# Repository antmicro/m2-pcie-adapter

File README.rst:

===========================
M.2 to PCIe x4 adapter card
===========================

Copyright (c) 2020-2021 Antmicro <`www.antmicro.com <https://www.antmicro.com>`_>

.. image:: img/pcie-adapter.jpg
   :scale: 40%

Overview
========

This repository contains open hardware design files for an adapter card created to expose the Peripheral Component Interconnect Express (PCIe) signals available on the M.2 (key M) connector in a regular PCIe x4 edge card socket.
This board has been designed as an extension of the Antmicro's `Jetson Nano Baseboard <https://github.com/antmicro/jetson-nano-baseboard>`_.
It allows the use of regular PCIe expansion cards and accessories with the NVIDIA `Jetson Nano <https://www.nvidia.com/en-us/autonomous-machines/embedded-systems/jetson-nano/>`_ and NVIDIA `Jetson Xavier NX <https://www.nvidia.com/en-us/autonomous-machines/embedded-systems/jetson-xavier-nx/>`_ system on modules.

Key features
============

* M.2 (key-M) edge connector
* PCIe x4 EdgeMount connector (Samtec PCIE-064-02-F-D-EMS2)
* external power supply connector (Molex 22053041)
* Nano Baseboard power supply pogo pins (Harwin P70-1000045R)

The PCB project files were prepared in KiCAD.

Board layout & dimensions
=========================

The picture below presents the general layout and dimensions of the PCB.

.. figure:: img/pcie-adapter-layout.png

Getting started
===============

The PCB design does not include any active components.
It simply passes the signals from the M.2 connector to the PCIe card edge socket.
The final thickness of the PCB should be 0.8mm to make it fit in the M.2 slots.
Since most PCIe card edge connectors are adjusted for 1.55mm, some mechanical tooling is required to assemble the PCIe socket on the PCB.

License
=======

`Apache-2.0 <LICENSE>`_

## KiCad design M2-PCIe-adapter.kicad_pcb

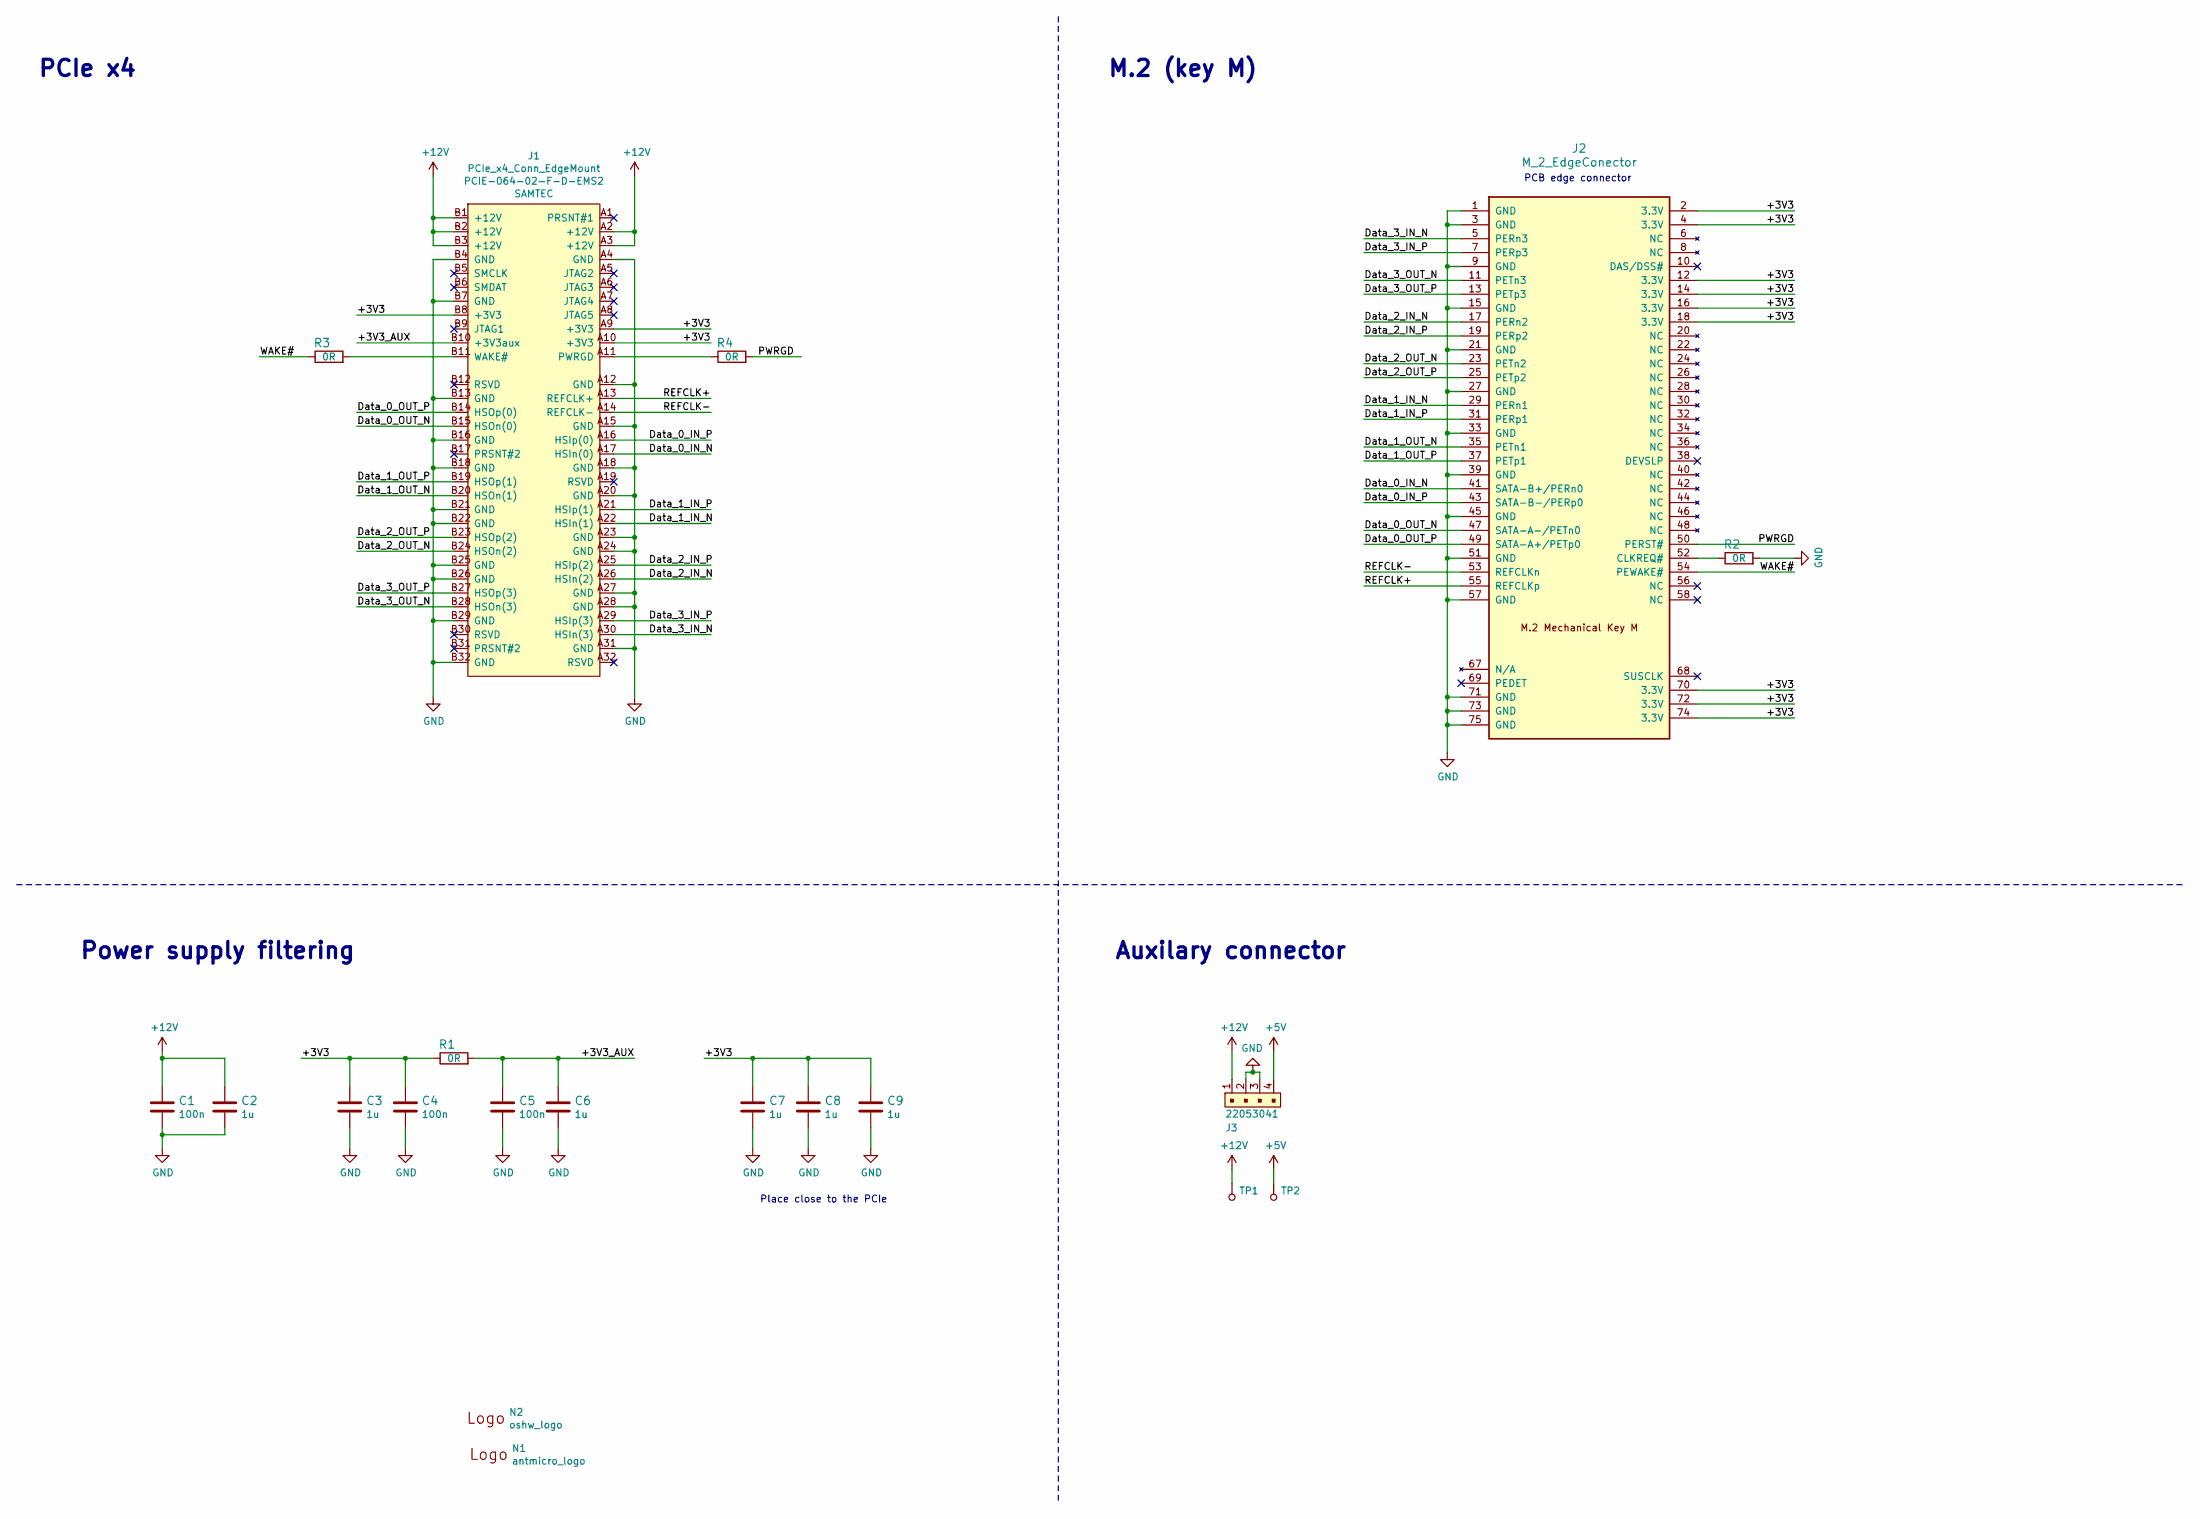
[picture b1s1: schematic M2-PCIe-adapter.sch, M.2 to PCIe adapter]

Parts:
C1, C4, C5: C_100n_0402_16V; 0402-cap; MPN MC0402B104K160CT
C2, C3, C6, C7, C8, C9: C_1u_0603; 0603-cap; MPN 0603X105K160CT
J1: PCIe_x4_Conn_EdgeMount; PCIE-064-02-X-D-EMSX; MPN PCIE-064-02-F-D-EMS2
J2: M_2_EdgeConector; M_2_EdgeConnector
J3: 22053041; MPN 22053041
N1: antmicro_logo; antmicro-logo_scaled_20mm
N2: oshw_logo; oshw-logo
R1, R2, R3, R4: R_0R_0402; 0402-res; MPN ERJ2GE0R00X
TP1, TP2: P70-1000045R; MPN P70-1000045R

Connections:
+5V: J3.4, TP2.1
+12V: C1.1, C2.1, J1.A2 (+12V), J1.A3 (+12V), J1.B1 (+12V), J1.B2 (+12V), J1.B3 (+12V), J3.1, TP1.1
/+3V3: C3.1, C4.1, C7.1, C8.1, C9.1, J1.A9 (+3V3), J1.A10 (+3V3), J1.B8 (+3V3), J2.2 (3.3V), J2.4 (3.3V), J2.12 (3.3V), J2.14 (3.3V), J2.16 (3.3V), J2.18 (3.3V), J2.70 (3.3V), J2.72 (3.3V), J2.74 (3.3V), R1.1
/+3V3_AUX: C5.1, C6.1, J1.B10 (+3V3aux), R1.2
/Data_0_IN_N: J1.A17 (HSIn(0)), J2.41 (SATA-B+/PERn0)
/Data_0_IN_P: J1.A16 (HSIp(0)), J2.43 (SATA-B-/PERp0)
/Data_0_OUT_N: J1.B15 (HSOn(0)), J2.47 (SATA-A-/PETn0)
/Data_0_OUT_P: J1.B14 (HSOp(0)), J2.49 (SATA-A+/PETp0)
/Data_1_IN_N: J1.A22 (HSIn(1)), J2.29 (PERn1)
/Data_1_IN_P: J1.A21 (HSIp(1)), J2.31 (PERp1)
/Data_1_OUT_N: J1.B20 (HSOn(1)), J2.35 (PETn1)
/Data_1_OUT_P: J1.B19 (HSOp(1)), J2.37 (PETp1)
/Data_2_IN_N: J1.A26 (HSIn(2)), J2.17 (PERn2)
/Data_2_IN_P: J1.A25 (HSIp(2)), J2.19 (PERp2)
/Data_2_OUT_N: J1.B24 (HSOn(2)), J2.23 (PETn2)
/Data_2_OUT_P: J1.B23 (HSOp(2)), J2.25 (PETp2)
/Data_3_IN_N: J1.A30 (HSIn(3)), J2.5 (PERn3)
/Data_3_IN_P: J1.A29 (HSIp(3)), J2.7 (PERp3)
/Data_3_OUT_N: J1.B28 (HSOn(3)), J2.11 (PETn3)
/Data_3_OUT_P: J1.B27 (HSOp(3)), J2.13 (PETp3)
/PWRGD: J2.50 (PERST#), R4.2
/REFCLK+: J1.A13 (REFCLK+), J2.55 (REFCLKp)
/REFCLK-: J1.A14 (REFCLK-), J2.53 (REFCLKn)
/WAKE#: J2.54 (PEWAKE#), R3.1
GND: C1.2, C2.2, C3.2, C4.2, C5.2, C6.2, C7.2, C8.2, C9.2, J1.A4 (GND), J1.A12 (GND), J1.A15 (GND), J1.A18 (GND), J1.A20 (GND), J1.A23 (GND), J1.A24 (GND), J1.A27 (GND), J1.A28 (GND), J1.A31 (GND), J1.B4 (GND), J1.B7 (GND), J1.B13 (GND), J1.B16 (GND), J1.B18 (GND), J1.B21 (GND), J1.B22 (GND), J1.B25 (GND), J1.B26 (GND), J1.B29 (GND), J1.B32 (GND), J2.1 (GND), J2.3 (GND), J2.9 (GND), J2.15 (GND), J2.21 (GND), J2.27 (GND), J2.33 (GND), J2.39 (GND), J2.45 (GND), J2.51 (GND), J2.57 (GND), J2.71 (GND), J2.73 (GND), J2.75 (GND), J3.2, J3.3, R2.2
unnamed: J1.A11 (PWRGD), R4.1
unnamed: J1.B11 (WAKE#), R3.2
unnamed: J2.52 (CLKREQ#), R2.1

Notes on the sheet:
Power supply filtering
Place close to the PCIe
PCIe x4
M.2 (key M)
PCB edge connector
Auxilary connector

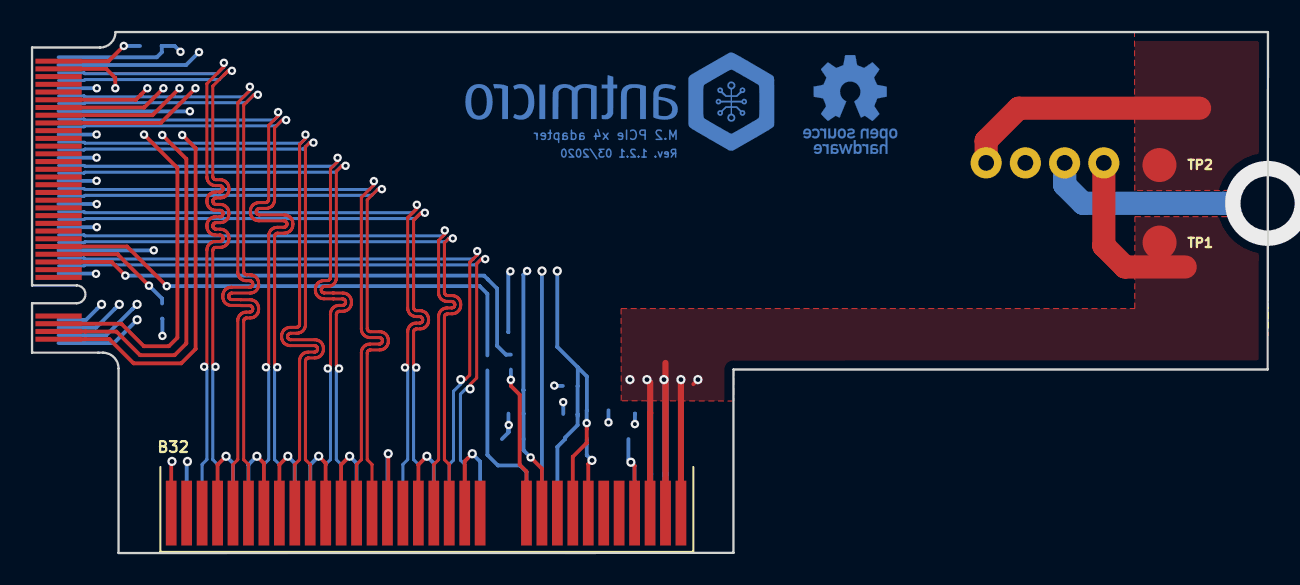
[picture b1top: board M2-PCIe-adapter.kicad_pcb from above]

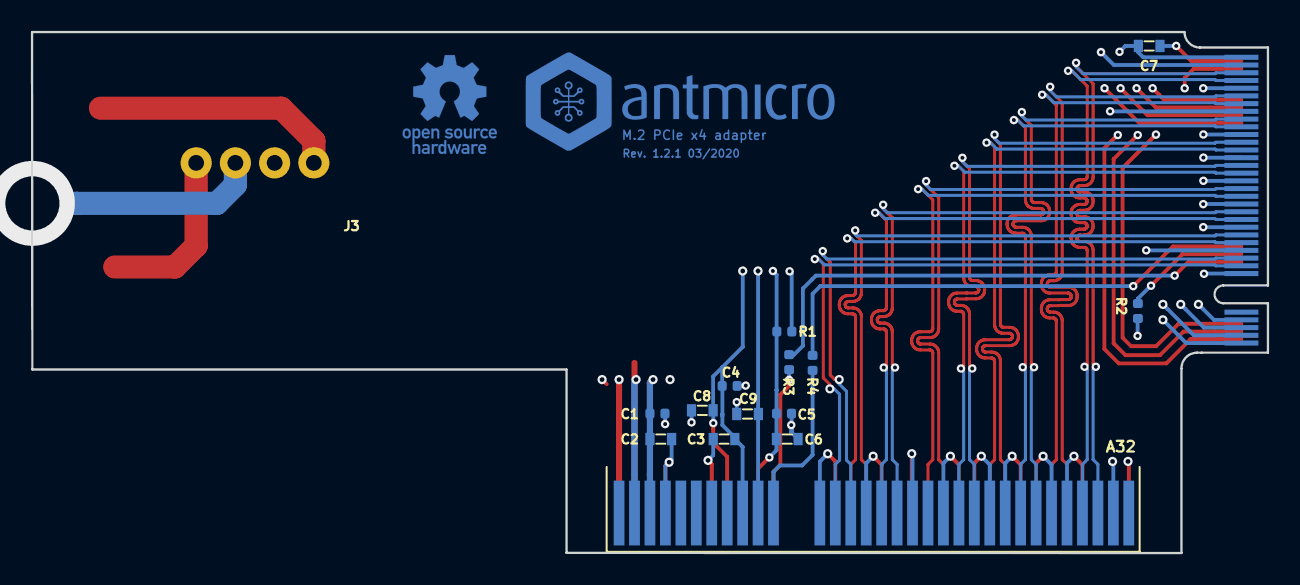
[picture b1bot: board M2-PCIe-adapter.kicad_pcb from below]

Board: 4 copper layers, 80.0 x 33.7 mm, 20 parts (16 on the bottom side), 28 nets.

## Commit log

2020-04-30 Update LICENSE
2020-04-30 Add design files for release 1.2.1
2020-04-30 Add README
2020-04-30 README: minor fix
2021-02-22 Add photo
2021-06-24 Notes added by 'git notes add'
